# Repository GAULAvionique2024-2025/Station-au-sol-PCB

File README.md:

# Station-au-sol-PCB
PCB Kicad pour la station au sol

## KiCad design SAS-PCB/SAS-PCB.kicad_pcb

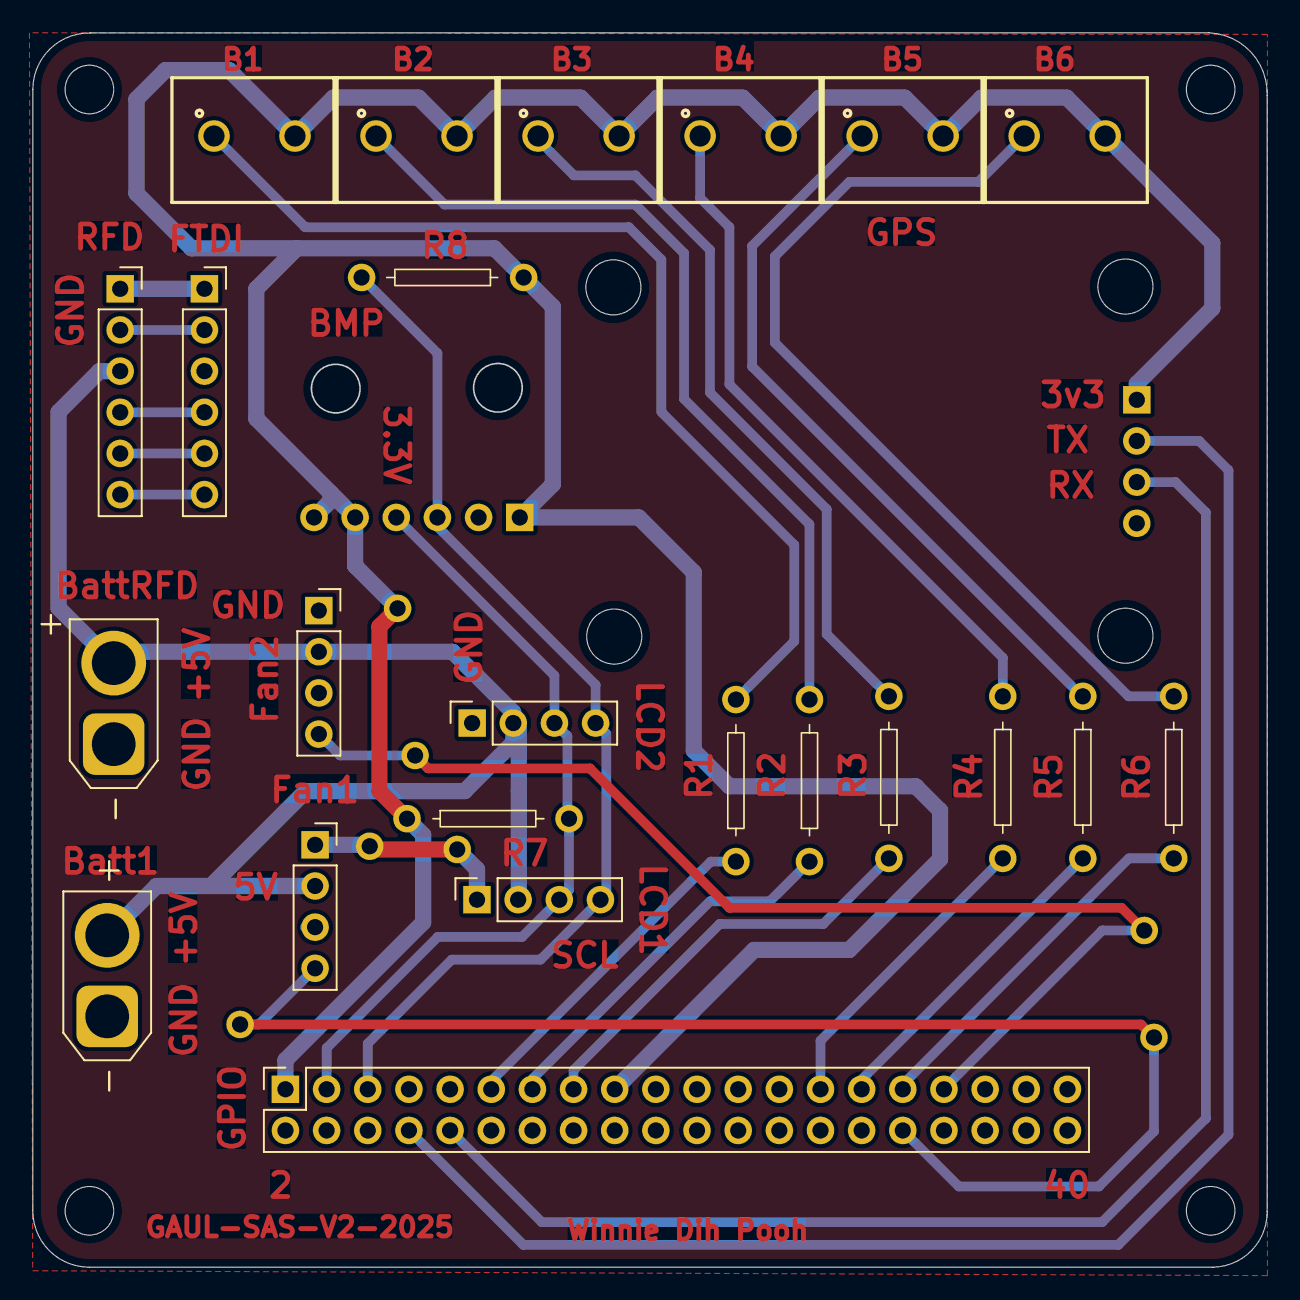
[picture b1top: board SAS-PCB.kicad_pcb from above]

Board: 2 copper layers, 76.2 x 76.2 mm, 26 parts (1 on the bottom side), 25 nets.

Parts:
3.3V: (no value)
Bouton_1, Bouton_2, Bouton_3, Bouton_4, Bouton_5, Bouton_6: 691137710002; bornie_2position
J1_Batt1, J7-RFD900x1: 691137710002; AMASS_XT30U-F_1x02_P5.0mm_Vertical
J2-LCD1, J3-LCD2, J8-Fan1, J9-Fan2: Conn_01x04_Socket; Conn_4_pos
J4-BMP280: Conn_01x06_Pin; Header-BMP280
J5-GPS1: Conn_01x04_Socket; conn-GPS
J6-cable-plat1: Conn_02x20_Odd_Even; PinSocket_2x20_P2.54mm_Vertical
J10-FTDI1, J10-FTDI2: Conn_01x06; Conn_6_pos
R1, R2, R3, R4, R5, R6, R7, R8: 1k; Resistance

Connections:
+3.3V: 3.3V.3.3V (Pin_4), Bouton_1.2 (5V), Bouton_2.2 (5V), Bouton_3.2 (5V), Bouton_4.2 (5V), Bouton_5.2 (5V), Bouton_6.2 (5V), J4-BMP280.1, J4-BMP280.5, J4-BMP280.6, J5-GPS1.1, J6-cable-plat1.1, J6-cable-plat1.17, R7.2, R8.2
+5V: J1_Batt1.2 (5V), J2-LCD1.2, J3-LCD2.2, J7-RFD900x1.2 (5V), J8-Fan1.2, J9-Fan2.2, J10-FTDI2.3
Bouton_1: J6-cable-plat1.11, R1.2
Bouton_2: J6-cable-plat1.13, R2.2
Bouton_3: J6-cable-plat1.15, R3.1
Bouton_4: J6-cable-plat1.27, R4.1
Bouton_5: J6-cable-plat1.29, R5.1
Bouton_6: J6-cable-plat1.31, R6.1
Fan1_PWM: J6-cable-plat1.32, J8-Fan1.4
Fan2_PWM: J6-cable-plat1.33, J9-Fan2.4
GND: J1_Batt1.1 (GND), J2-LCD1.1, J3-LCD2.1, J4-BMP280.2, J5-GPS1.4, J6-cable-plat1.6, J6-cable-plat1.9, J6-cable-plat1.14, J6-cable-plat1.20, J6-cable-plat1.25, J6-cable-plat1.30, J6-cable-plat1.34, J6-cable-plat1.39, J7-RFD900x1.1 (GND), J8-Fan1.1, J9-Fan2.1, J10-FTDI1.1, J10-FTDI2.1
unnamed: Bouton_1.1 (GND), R1.1
unnamed: Bouton_2.1 (GND), R2.1
unnamed: Bouton_3.1 (GND), R3.2
unnamed: Bouton_4.1 (GND), R4.2
unnamed: Bouton_5.1 (GND), R5.2
unnamed: Bouton_6.1 (GND), R6.2
RFD_CTS: J10-FTDI1.2, J10-FTDI2.2
RFD_RTS: J10-FTDI1.6, J10-FTDI2.6
RFD_RX: J10-FTDI1.4, J10-FTDI2.4
RFD_TX: J10-FTDI1.5, J10-FTDI2.5
RXD: J5-GPS1.3, J6-cable-plat1.10
SCL: J2-LCD1.4, J3-LCD2.4, J4-BMP280.3, J6-cable-plat1.5, R8.1
SDA: J2-LCD1.3, J3-LCD2.3, J4-BMP280.4, J6-cable-plat1.3, R7.1
TXD: J5-GPS1.2, J6-cable-plat1.8

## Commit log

2025-01-18 Création de projet Kicad 8.0.7
2025-01-18 Ajout de librairies
2025-01-18 Ajout de composantes sur le schema
2025-01-26 schematic done
2025-01-27 petites modifs
2025-01-28 Rooting terminé
    Reste à refaire les mounting holes et enlever les bouttes de cuivre trop mince.
2025-01-28 Header Fix
2025-01-28 Modification des power plane, corrections DRC et extraction des fichiers gerber
2025-03-15 Add files via upload
    Version 1 du PCB de la station au sol
2025-03-17 U2
    trial 2
2025-03-31 Version_a_amiliorer
    pas tant fonctionnel
2025-03-31 Version_préliminaire
    version préliminaire: fil jumper nécessaire pour certaines connections(moins de 5)
2025-03-31 Corrections mineures
2025-04-02 Version_presque_fini
    Trace fini avec via, augmentation de l'ecriture. Il reste seulement les power plane pour 3.3V et 5V.
2025-04-02 Version_fini
    Ajouter les zones: ground, 5V, 3V3
2025-04-03 Modification de trace 3.3V
2025-05-01 A_verifier_demain
    Abandon du RPM tachymetre pour le mieux.
2025-05-01 Version_2_final
    Version envoyer en impression
